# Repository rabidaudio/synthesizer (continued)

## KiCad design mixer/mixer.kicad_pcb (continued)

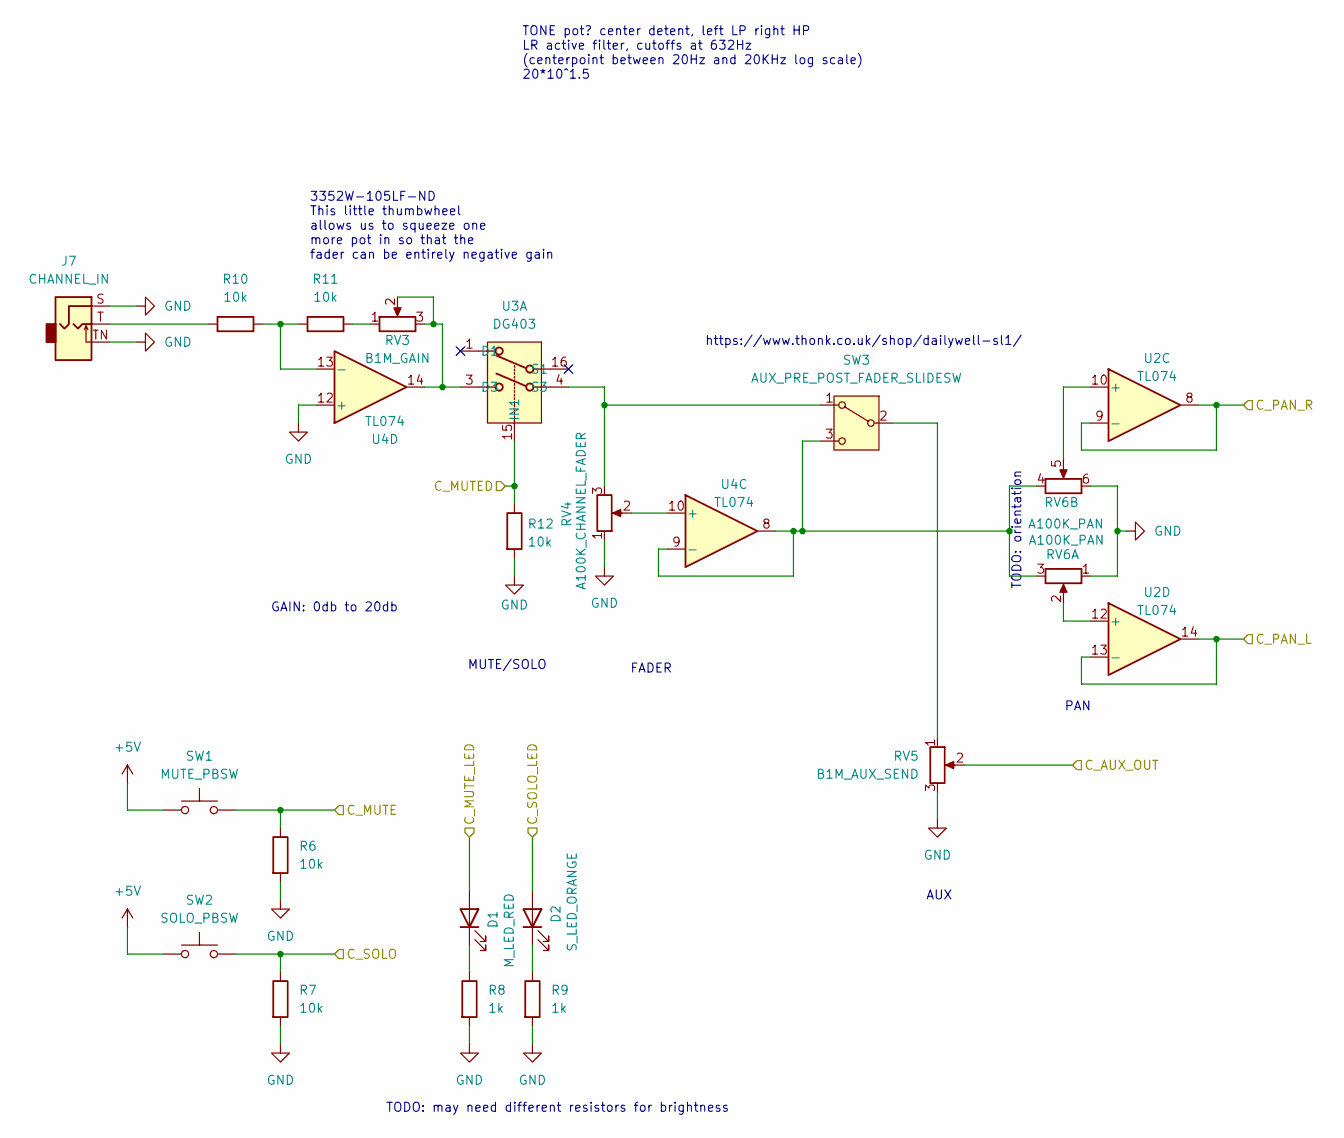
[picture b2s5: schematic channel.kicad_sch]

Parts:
D1: M_LED_RED; LED_D2.0mm_W4.8mm_H2.5mm_FlatTop
D2: S_LED_ORANGE; LED_D2.0mm_W4.8mm_H2.5mm_FlatTop
J7: CHANNEL_IN; Jack_3.5mm_QingPu_WQP-PJ398SM_Vertical_CircularHoles
R6, R7, R10, R11, R12: 10k; R_0603_1608Metric
R8, R9: 1k; R_0603_1608Metric
RV3: B1M_GAIN; 3352W
RV4: A100K_CHANNEL_FADER; Potentiometer_Bourns_PTA3043_Single_Slide
RV5: B1M_AUX_SEND; Potentiometer_Alpha_RD901F-40-00D_Single_Vertical
RV6: A100K_PAN; Potentiometer_Alpha_RD902F-40-00D_Dual_Vertical_CircularHol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
SW1: MUTE_PBSW; SW_PUSH_6mm
SW2: SOLO_PBSW; SW_PUSH_6mm
SW3: AUX_PRE_POST_FADER_SLIDESW; Dailywell SPDT Sub-Mini Slide SW
U2, U4: TL074; SOIC-14_3.9x8.7mm_P1.27mm
U3: DG403; SOIC-16_3.9x9.9mm_P1.27mm

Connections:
+5V: SW1.1, SW2.1; also elsewhere on the board
/Channel Module/C1_MUTE: R6.1, SW1.2; also elsewhere on the board
/Channel Module/C1_MUTED: R12.1, U3.15 (IN1); also elsewhere on the board
/Channel Module/C1_MUTE_LED: D1.2 (A); also elsewhere on the board
/Channel Module/C1_SOLO: R7.1, SW2.2; also elsewhere on the board
/Channel Module/C2_MUTED: U3.10 (IN2); also elsewhere on the board
/Channel Module/C2_MUTE_LED: D2.2 (A); also elsewhere on the board
/Channel Module/Channel1/C_AUX_OUT: RV5.2; also elsewhere on the board
/Channel Module/Channel1/C_PAN_L: U2.13 (-), U2.14; also elsewhere on the board
/Channel Module/Channel1/C_PAN_R: U2.8, U2.9 (-); also elsewhere on the board
/Channel Module/Channel2/C_PAN_L: U2.1, U2.2 (-); also elsewhere on the board
/Channel Module/Channel2/C_PAN_R: U2.6 (-), U2.7; also elsewhere on the board
GND: J7.S, J7.TN, R6.2, R7.2, R8.2, R9.2, R12.2, RV4.1, RV5.3, RV6.1, RV6.6, U4.3 (+), U4.12 (+); also elsewhere on the board
unnamed: D1.1 (K), R8.1
unnamed: D2.1 (K), R9.1
unnamed: J7.T, R10.1
unnamed: R11.2, RV3.1
unnamed: RV4.3, SW3.1 (A), U3.4 (S3)
unnamed: RV5.1, SW3.2 (B)
unnamed: RV6.3, RV6.4, SW3.3 (C), U4.8, U4.9 (-)
unnamed 55: U3.5 (S4); also elsewhere on the board
unnamed 57: U4.6 (-), U4.7; also elsewhere on the board
unnamed 58: U2.3 (+); also elsewhere on the board
unnamed 59: U2.5 (+); also elsewhere on the board
unnamed: RV6.5, U2.10 (+)
unnamed: RV6.2, U2.12 (+)
unnamed: RV3.2, RV3.3, U3.3 (D3), U4.14
unnamed 63: U3.6 (D4), U4.1; also elsewhere on the board
unnamed 64: U4.2 (-); also elsewhere on the board
unnamed 65: U4.5 (+); also elsewhere on the board
unnamed: RV4.2, U4.10 (+)
unnamed: R10.2, R11.1, U4.13 (-)

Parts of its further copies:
D3: M_LED_RED; LED_D2.0mm_W4.8mm_H2.5mm_FlatTop
D4: S_LED_ORANGE; LED_D2.0mm_W4.8mm_H2.5mm_FlatTop
J9: CHANNEL_IN; Jack_3.5mm_QingPu_WQP-PJ398SM_Vertical_CircularHoles
R25, R26, R29, R30, R31: 10k; R_0603_1608Metric
R27, R28: 1k; R_0603_1608Metric
RV7: B1M_GAIN; 3352W
RV8: A100K_CHANNEL_FADER; Potentiometer_Bourns_PTA3043_Single_Slide
RV9: B1M_AUX_SEND; Potentiometer_Alpha_RD901F-40-00D_Single_Vertical
RV10: A100K_PAN; Potentiometer_Alpha_RD902F-40-00D_Dual_Vertical_CircularHol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
SW4: MUTE_PBSW; SW_PUSH_6mm
SW5: SOLO_PBSW; SW_PUSH_6mm
SW6: AUX_PRE_POST_FADER_SLIDESW; Dailywell SPDT Sub-Mini Slide SW

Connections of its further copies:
+5V: SW4.1, SW5.1; also elsewhere on the board
/Channel Module/C1_SOLO_LED: D3.2 (A); also elsewhere on the board
/Channel Module/C2_MUTE: R25.1, SW4.2; also elsewhere on the board
/Channel Module/C2_MUTED: R31.1; also elsewhere on the board
/Channel Module/C2_SOLO: R26.1, SW5.2; also elsewhere on the board
/Channel Module/C2_SOLO_LED: D4.2 (A); also elsewhere on the board
/Channel Module/Channel2/C_AUX_OUT: RV9.2; also elsewhere on the board
GND: J9.S, J9.TN, R25.2, R26.2, R27.2, R28.2, R31.2, RV8.1, RV9.3, RV10.1, RV10.6; also elsewhere on the board
unnamed: D3.1 (K), R27.1
unnamed: D4.1 (K), R28.1
unnamed: J9.T, R29.1
unnamed: R30.2, RV7.1
unnamed 55: RV8.3, SW6.1 (A); also elsewhere on the board
unnamed: RV9.1, SW6.2 (B)
unnamed 57: RV10.3, RV10.4, SW6.3 (C); also elsewhere on the board
unnamed 58: RV10.2; also elsewhere on the board
unnamed 59: RV10.5; also elsewhere on the board
unnamed 63: RV7.2, RV7.3; also elsewhere on the board
unnamed 64: R29.2, R30.1; also elsewhere on the board
unnamed 65: RV8.2; also elsewhere on the board

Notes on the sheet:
MUTE/SOLO
PAN
TODO: orientation
GAIN: 0db to 20db
AUX
FADER
3352W-105LF-ND This little thumbwheel allows us to squeeze one more pot in so that the fader can be entirely negative gain
TODO: may need different resistors for brightness
TONE pot? center detent, left LP right HP LR active filter, cutoffs at 632Hz (centerpoint between 20Hz and 20KHz log scale) 20*10^1.5
https://www.thonk.co.uk/shop/dailywell-sl1/

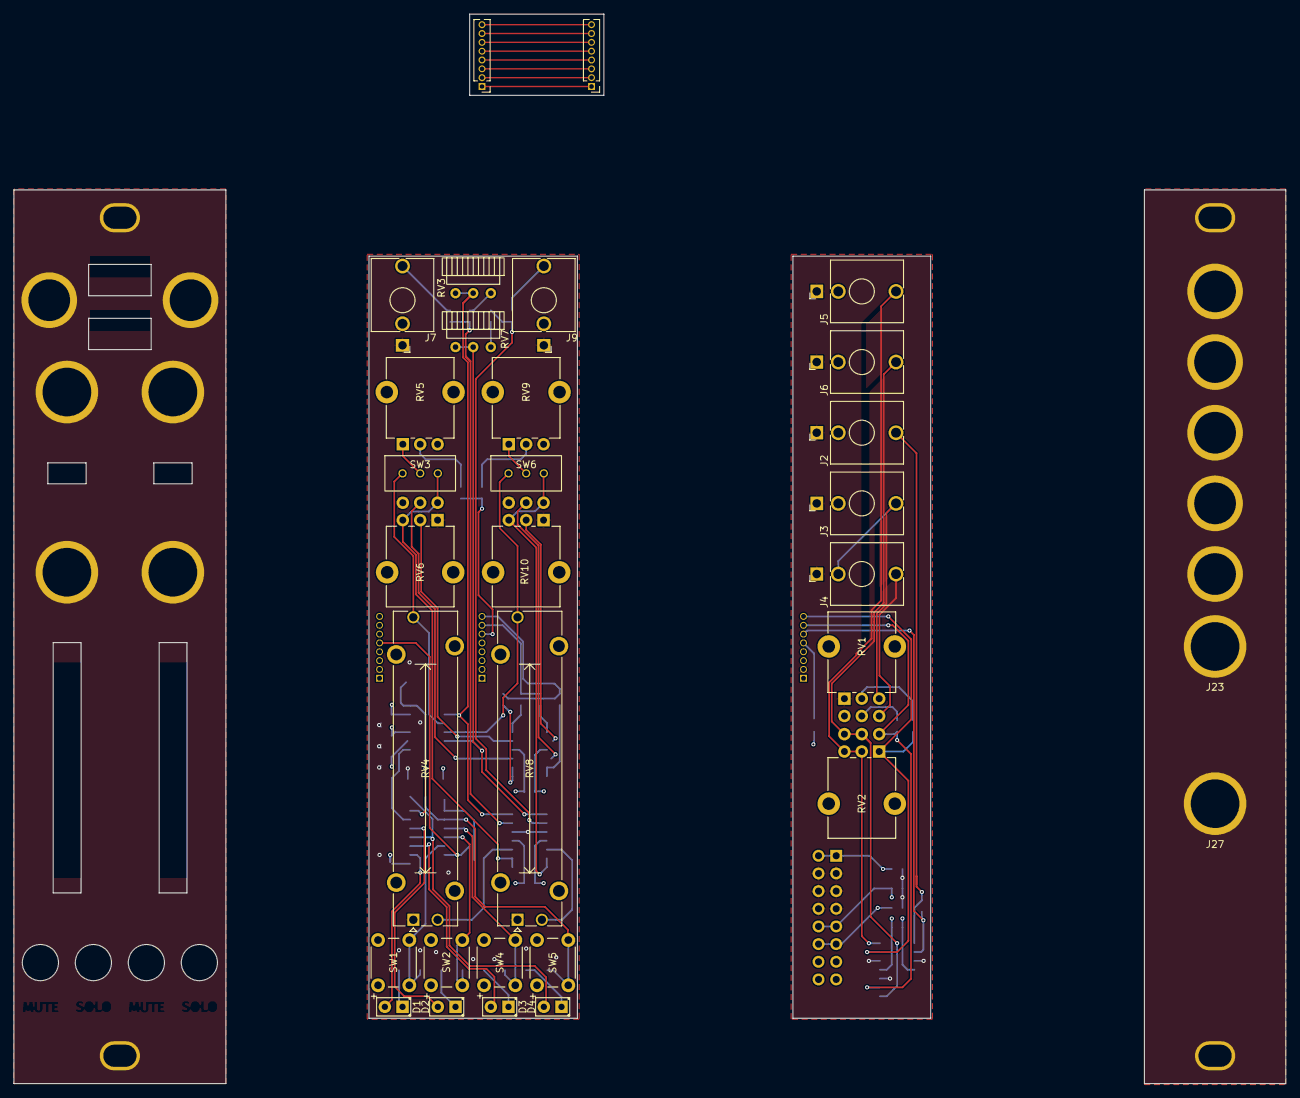
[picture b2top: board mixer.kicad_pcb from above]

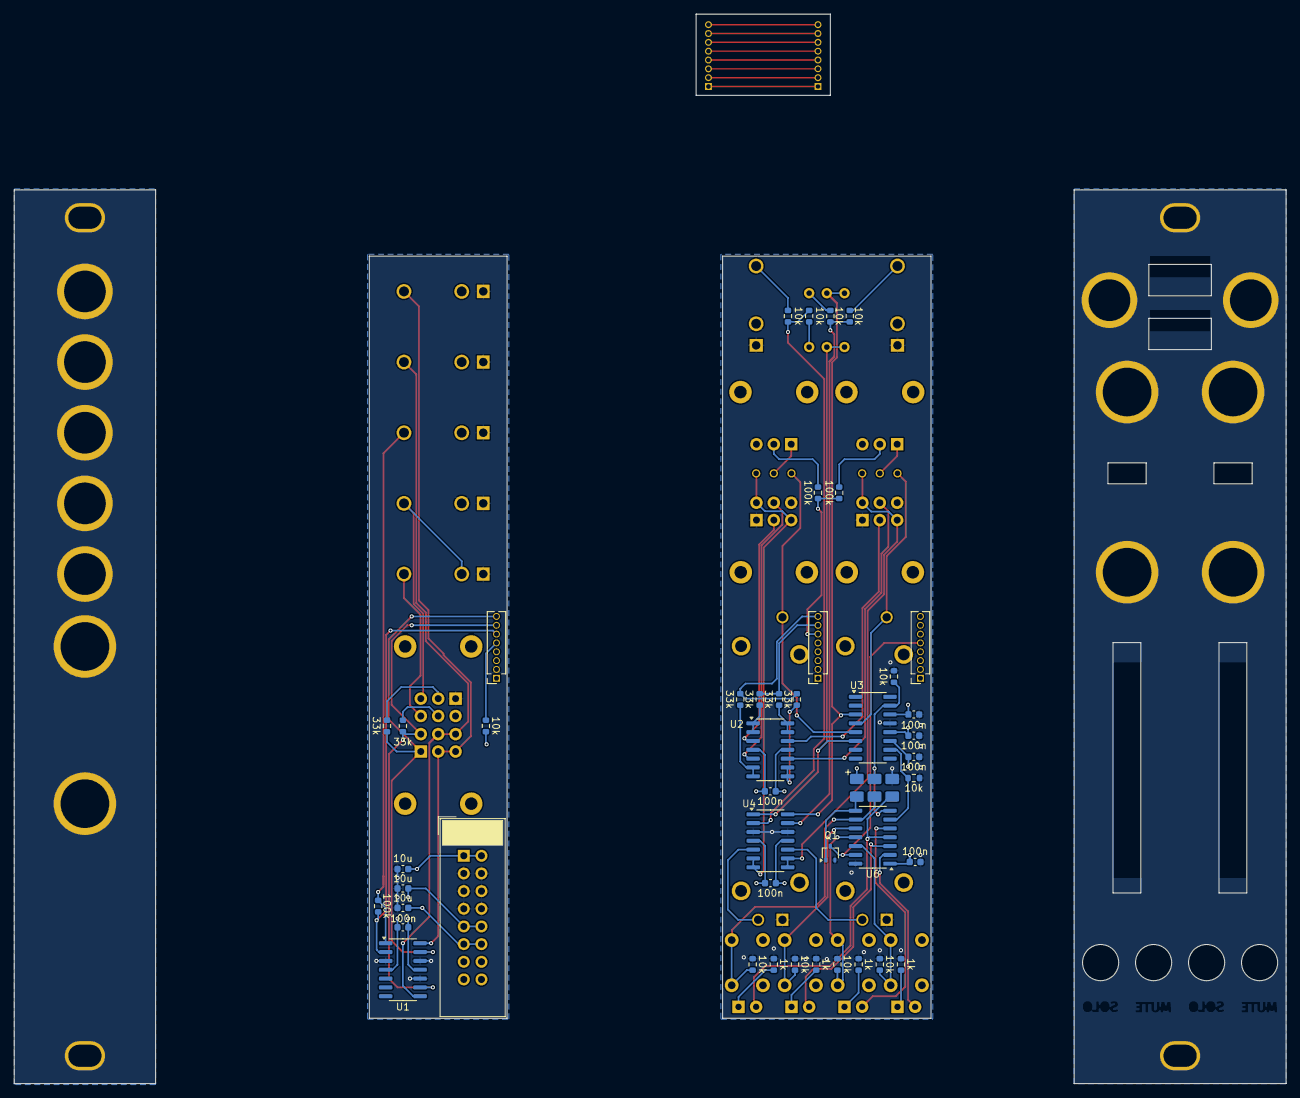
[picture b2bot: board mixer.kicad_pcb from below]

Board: 4 copper layers, 182.9 x 153.8 mm, 99 parts (45 on the bottom side), 68 nets.

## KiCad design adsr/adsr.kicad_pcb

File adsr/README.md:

# ADSR Envelope

This circuit operates by using the LM13700 as a variable current source charging
a capacitor. It is configured as a non-inverting op-amp charging the capacitor
to a reference voltage `V_ref` at the `+` pin with a slew rate limited by the current
control. The capacitor's voltage will change linearly based on `I_abc` until it settles
at `V_ref`. Then a bit of digital logic to create a 3-state state machine to select the
correct  `V_ref` and `I_abc`.

States:

- Attack: `V_gate=5V`, `V_ref=V_in`, `I_abc` controlled by `R_attack`
- Decay: `V_gate=5V`, `V_ref=V_sustain`, `I_abc` controlled by `R_decay`
- Release: `V_gate=0`, `V_ref=0`, `I_abc` controlled by `R_release`

The Attack, Decay, and Release knobs control `I_abc` in each state,
while the Sustain knob divides down `V_in` to set `V_ref` in the
Decay state.

A comparator, capacitor, and a few transistors create cheap analog
a flip-flop that turns on when the output hits `V_in` (flipping from
the Attack state to the Decay state), and turns off when `V_gate`
turns off.

Voltage control of the parameters could be possible by exposing
access to `I_abc`, but it doesn't make much sense to me to expose
those parameters with any control other than a knob - it's not the
kind of thing you need to modulate automatically.

Choice of the capacitor and the knob resistance control the time
range. Large values for both mean a longer charge time, but a large
capacitance effects the fastest charge time too, since `I_abc` is
capped at 2mA. Pot size effects dynamic range.

In practice, charge times less than 15ms are undetectable, and charge times above 2s are largely unnecessary.

A non-linear resistance would allow finer control at larger charge times. However linear seems to have plenty of expressiveness.

C=4.7u and a knob range of 1M gives a control range of 12ms to \~1.8s for a
0-5V change, i.e. a slew rate between 356 V/s and 2.4 V/s.

Could offer two caps, fast and slow, with a toggle switch. A 22u capacitor gives 58ms to 8.6s. A 1u capacitor gives \~5ms to \~55ms.

A current mirror isolates the 3 different reference voltages, without it they
interfere with each other.

Rates are dependant on the input level. This means if the input gate level is variable (for example it depends on MIDI note velocity), then the times will be slower for harder hits. We'd probably want constant rates regardless of velocity for example. However this seems difficult to achieve with the current design, as during release the input voltage is off, so without memory you don't have a reference to scale the output by.

**TODO: power usage**

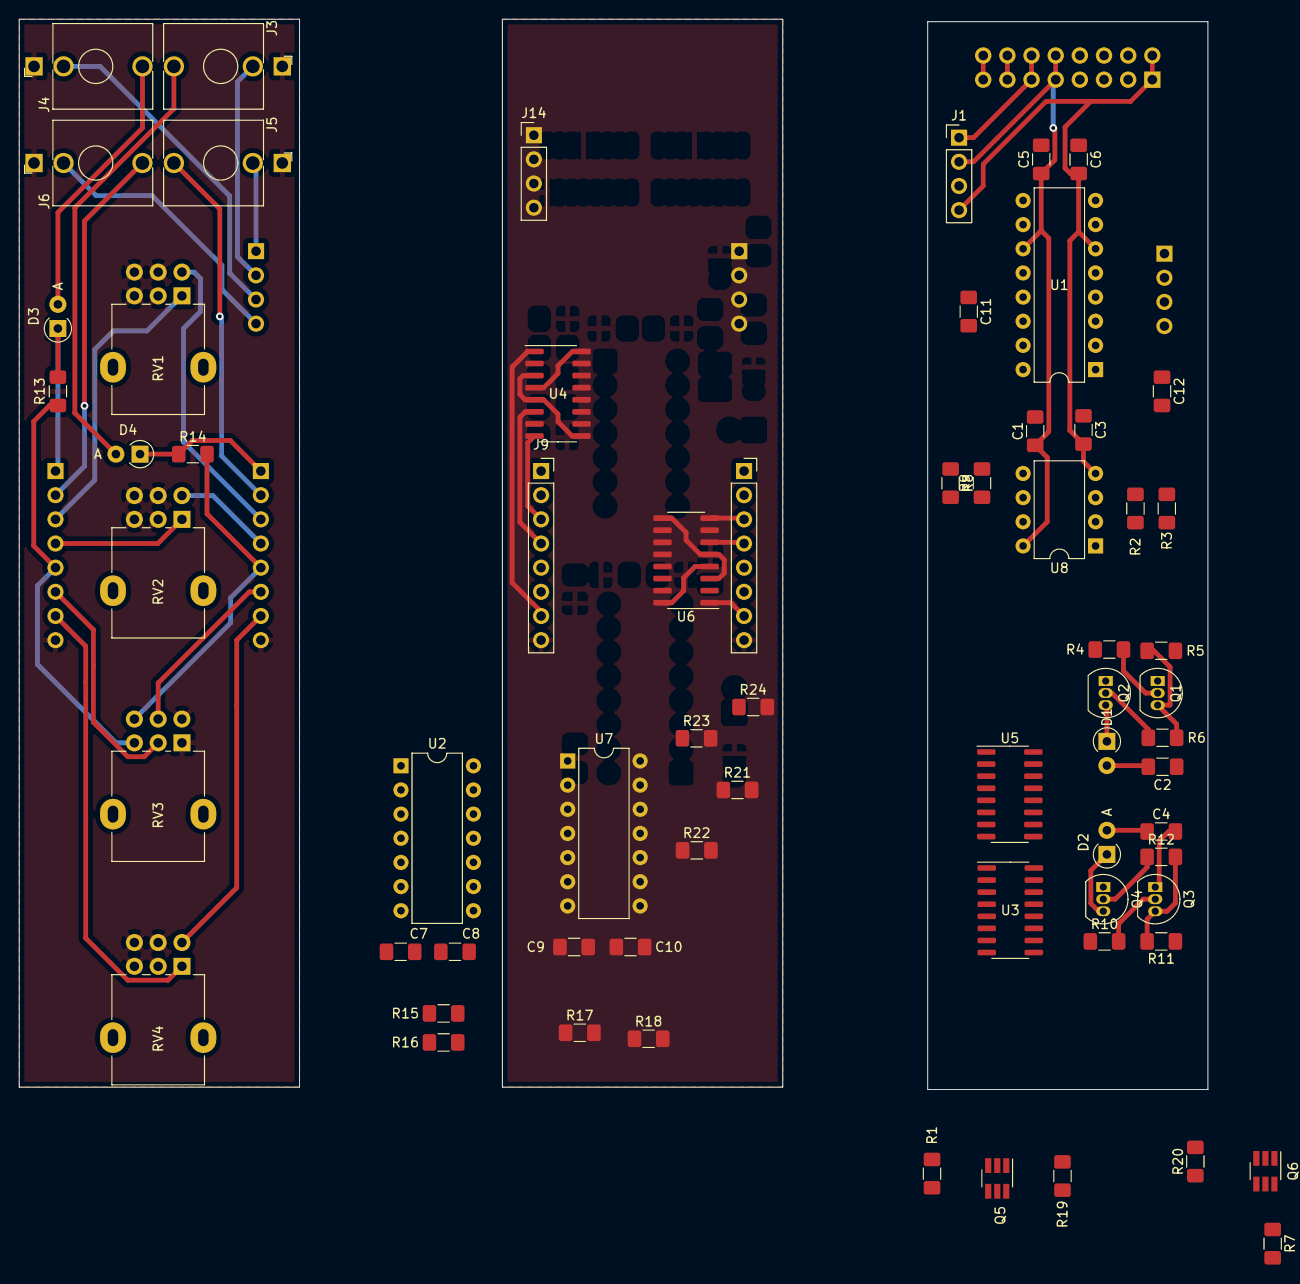
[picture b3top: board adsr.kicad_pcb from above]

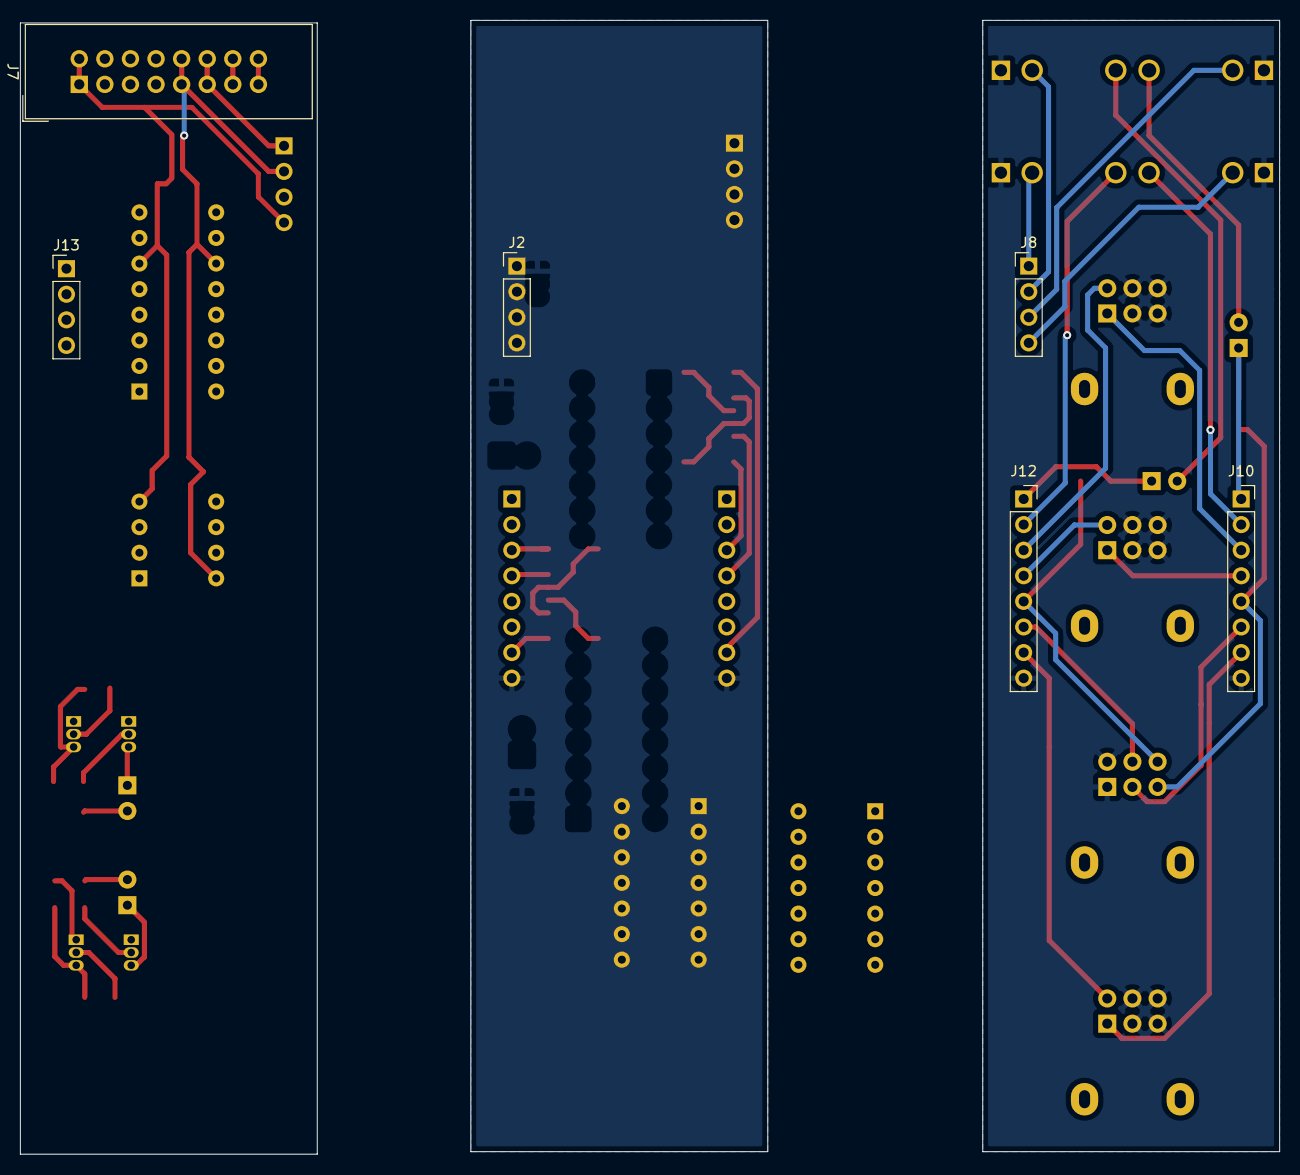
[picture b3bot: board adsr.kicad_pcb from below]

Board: 2 copper layers, 125.0 x 112.5 mm, 72 parts (6 on the bottom side), 64 nets.

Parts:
C1, C3, C5, C6, C7, C8, C9, C10: 0.1u; C_1206_3216Metric_Pad1.42x1.75mm_HandSolder
C2, C4: 100n; C_1206_3216Metric_Pad1.42x1.75mm_HandSolder
C11, C12: 4.7u; C_1206_3216Metric_Pad1.42x1.75mm_HandSolder
D1, D2, D3, D4: D; D_A-405_P2.54mm_Vertical_AnodeUp
J1: Conn_01x04_Female; PinHeader_1x04_P2.54mm_Vertical
J2, J8, J13, J14: Conn_01x04_Male; PinHeader_1x04_P2.54mm_Vertical
J3: B_IN; Jack_3.5mm_QingPu_WQP-PJ398SM_Vertical_CircularHoles
J4: A_IN; Jack_3.5mm_QingPu_WQP-PJ398SM_Vertical_CircularHoles
J5: B_OUT; Jack_3.5mm_QingPu_WQP-PJ398SM_Vertical_CircularHoles
J6: A_OUT; Jack_3.5mm_QingPu_WQP-PJ398SM_Vertical_CircularHoles
J7: EURORACK_CONN_16; EURORACK_16_IDC
J9, J11: Conn_01x08_Female; PinSocket_1x08_P2.54mm_Vertical
J10, J12: Conn_01x08_Male; PinSocket_1x08_P2.54mm_Vertical
Q1, Q2, Q3, Q4: 2N3904; TO-92_Inline
Q5, Q6: DMMT5401; SOT-23-6_Handsoldering
R1, R7, R19, R20: 6.8k; R_1206_3216Metric_Pad1.42x1.75mm_HandSolder
R2, R6, R8, R12, R21, R23: 1K; R_1206_3216Metric_Pad1.42x1.75mm_HandSolder
R3, R4, R5, R9, R10, R11, R22, R24: 100K; R_1206_3216Metric_Pad1.42x1.75mm_HandSolder
R13, R14: 1M; R_1206_3216Metric_Pad1.42x1.75mm_HandSolder
R15, R16, R17, R18: 10K; R_1206_3216Metric_Pad1.42x1.75mm_HandSolder
RV1: R_ATTACK; Potentiometer_Alpha_RD902F-40-00D_Dual_Vertical
RV2: R_DECAY; Potentiometer_Alpha_RD902F-40-00D_Dual_Vertical
RV3: R_SUSTAIN; Potentiometer_Alpha_RD902F-40-00D_Dual_Vertical
RV4: R_RELEASE; Potentiometer_Alpha_RD902F-40-00D_Dual_Vertical
U1: LM13700; DIP-16_W7.62mm
U2, U7: TL074; DIP-14_W7.62mm
U3, U4, U5, U6: DG403; SOIC-16_3.9x9.9mm_P1.27mm
U8: TL072; DIP-8_W7.62mm

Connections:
+5V: J1.1, J7.11 (5V), J14.4, U3.12 (VL), U4.12 (VL), U5.12 (VL), U6.12 (VL)
+12V: C1.1, C5.1, C7.1, C9.1, J1.2, J7.9 (12V_P), J14.3, Q5.5 (E2), Q5.6 (E1), Q6.5 (E2), Q6.6 (E1), R5.1, R11.1, R22.2, R24.2, U1.11 (V+), U2.4 (V+), U3.11 (V+), U4.11 (V+), U5.11 (V+), U6.11 (V+), U7.4 (V+), U8.8 (V+)
-12V: C3.2, C6.2, C8.2, C10.2, J1.4, J7.1 (12V_N), J14.1, U1.6 (V-), U2.11 (V-), U3.14 (V-), U4.14 (V-), U5.14 (V-), U6.14 (V-), U7.11 (V-), U8.4 (V-)
/envelope/ATTACK: J9.3, J10.3, RV1.1, U4.8 (D2)
/envelope/DECAY: J9.4, J10.4, RV2.1, U4.6 (D4)
/envelope/IN_RAW: D3.1 (K), J9.1, J10.1, R13.1, U2.12 (+)
/envelope/REF: R2.1, U2.1, U2.2 (-), U3.8 (D2)
/envelope/REF_RAW: J9.5, J10.5, R13.2, RV3.3, U2.3 (+)
/envelope/RELEASE: J9.7, J10.7, RV4.1, U4.1 (D1)
/envelope/STATE: C2.1, D1.2 (A), U1.9, U3.10 (IN2), U4.10 (IN2)
/envelope/SUS: U2.6 (-), U2.7, U3.6 (D4)
/envelope/SUS_RAW: J9.6, J10.6, RV3.2, U2.5 (+)
/envelope/VC: C11.1, U1.12, U1.13 (-), U2.10 (+), U8.3 (+)
/envelope/VINS: R4.1, U2.14, U3.15 (IN1), U4.15 (IN1)
/sheet5F5D80AF/ATTACK: J11.3, J12.3, RV1.4, U6.8 (D2)
/sheet5F5D80AF/DECAY: J11.4, J12.4, RV2.4, U6.6 (D4)
/sheet5F5D80AF/IN_RAW: D4.1 (K), J11.1, J12.1, R14.1, U7.5 (+)
/sheet5F5D80AF/REF: R8.1, U5.8 (D2), U7.8, U7.9 (-)
/sheet5F5D80AF/REF_RAW: J11.5, J12.5, R14.2, RV3.6, U7.10 (+)
/sheet5F5D80AF/RELEASE: J11.7, J12.7, RV4.4, U6.1 (D1)
/sheet5F5D80AF/STATE: C4.1, D2.2 (A), U1.8, U5.10 (IN2), U6.10 (IN2)
/sheet5F5D80AF/SUS: U5.6 (D4), U7.13 (-), U7.14
/sheet5F5D80AF/SUS_RAW: J11.6, J12.6, RV3.5, U7.12 (+)
/sheet5F5D80AF/VC: C12.1, U1.4 (-), U1.5, U7.3 (+), U8.5 (+)
/sheet5F5D80AF/VINS: R10.1, U5.15 (IN1), U6.15 (IN1), U7.7
A_IN: D3.2 (A), J4.T
A_IN_DEFAULT: J2.3, J4.TN, J8.3, J13.3
A_OUT: J6.T, J9.2, J10.2, R16.2, U2.8
A_OUT_DEFAULT: J2.4, J6.TN, J8.4, J13.4
B_IN: D4.2 (A), J3.T
B_IN_DEFAULT: J2.2, J3.TN, J8.2, J13.2
B_OUT: J5.T, J11.2, J12.2, R18.2, U7.1
B_OUT_DEFAULT: J2.1, J5.TN, J8.1, J13.1
GND: C1.2, C2.2, C3.1, C4.2, C5.2, C6.1, C7.2, C8.1, C9.2, C10.1, C11.2, C12.2, J1.3, J3.S, J4.S, J5.S, J6.S, J7.3 (GND), J9.8, J10.8, J11.8, J12.8, J14.2, Q1.1 (E), Q2.1 (E), Q3.1 (E), Q4.1 (E), R3.2, R9.2, R15.1, R17.1, R21.2, R23.2, RV1.2, RV1.3, RV1.5, RV1.6, RV2.2, RV2.3, RV2.5, RV2.6, RV3.1, RV3.4, RV4.2, RV4.3, RV4.5, RV4.6, U3.1 (D1), U3.13 (GND), U4.13 (GND), U5.1 (D1), U5.13 (GND), U6.13 (GND)
unnamed: D1.1 (K), Q2.3 (C)
unnamed: D2.1 (K), Q4.3 (C)
unnamed: Q1.2 (B), R4.2
unnamed: Q1.3 (C), R5.2, R6.2
unnamed: Q2.2 (B), R6.1
unnamed: Q3.2 (B), R10.2
unnamed: Q3.3 (C), R11.2, R12.2
unnamed: Q4.2 (B), R12.1
unnamed: Q5.1 (C1), Q5.2 (B1), Q5.3 (B2), R19.1
unnamed: Q5.4 (C2), R1.1
unnamed: Q6.1 (C1), Q6.2 (B1), Q6.3 (B2), R20.1
unnamed: Q6.4 (C2), R7.1
unnamed: R1.2, U1.16
unnamed: R2.2, R3.1, U8.2 (-)
unnamed: R7.2, U1.1
unnamed: R8.2, R9.1, U8.6 (-)
unnamed: R15.2, R16.1, U2.9 (-)
unnamed: R17.2, R18.1, U7.2 (-)
unnamed: R19.2, U4.4 (S3), U4.16 (S1)
unnamed: R20.2, U6.4 (S3), U6.16 (S1)
unnamed: R21.1, R22.1, U2.13 (-)
unnamed: R23.1, R24.1, U7.6 (-)
unnamed: U1.3 (+), U5.4 (S3), U5.16 (S1)
unnamed: U1.7, U8.7
unnamed: U1.10, U8.1
unnamed: U1.14 (+), U3.4 (S3), U3.16 (S1)
unnamed: U3.3 (D3), U3.5 (S4), U3.9 (S2)
unnamed: U4.3 (D3), U4.5 (S4), U4.9 (S2)
unnamed: U5.3 (D3), U5.5 (S4), U5.9 (S2)
unnamed: U6.3 (D3), U6.5 (S4), U6.9 (S2)

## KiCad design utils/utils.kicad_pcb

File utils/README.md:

# Jackknife

> Buffer/Inverter/Gate/Adder/Scaler/Source

## Description

This is a collection of common tools for transforming signals, either control voltages or audio signals. While there are several distinct utilities, most are not mutually-exclusive.

### Source

When `A_IN` is disconnected, `OUT` is a constant voltage output based on the position of the knob. `OUT` is 0V when the knob is in the center position, and adjusts up to +/- 10V.

### Buffer / Scaler

When `A_IN` is supplied, it's value is buffered to `OUT`. The knob position linearly adjusts the output gain. At the center position, `OUT` is the same as `A_IN`. At the full-left position, `OUT` is off. At the full-right position, the value of `A_IN` is doubled. 

### Adder

When `B_IN` is supplied, it's value is added to `A_IN` before applying scaling.

### Inverter

`~OUT` is always the inverse of `OUT`.

### Gate

When `GATE` is supplied with a digital voltage, it allows disabling `OUT` (and `~OUT`) at logic-low (0V). An LED indicates when the gate is open. When `GATE` is not supplied, the outputs are always enabled, and the LED remains off.

### Digital logic

Digital `OR` can be implemented by summing signals on `A_IN` and `B_IN` With the knob at the 1/4 position. Digital `AND` can be implemented by applying one signal to `A_IN` and one to `GATE` with the knob at the 1/2 position.

## Design

A summing inverting amplifier with a variable feedback resistor handles the adder, inverter, and scalar. A connection on either A or B toggles an analog switch selecting between a constant voltage source and the summing output. Another
analog switch controlled by the gate allows that signal to be toggled before it is buffered in both an inverted and
re-inverted back to positive outputs.

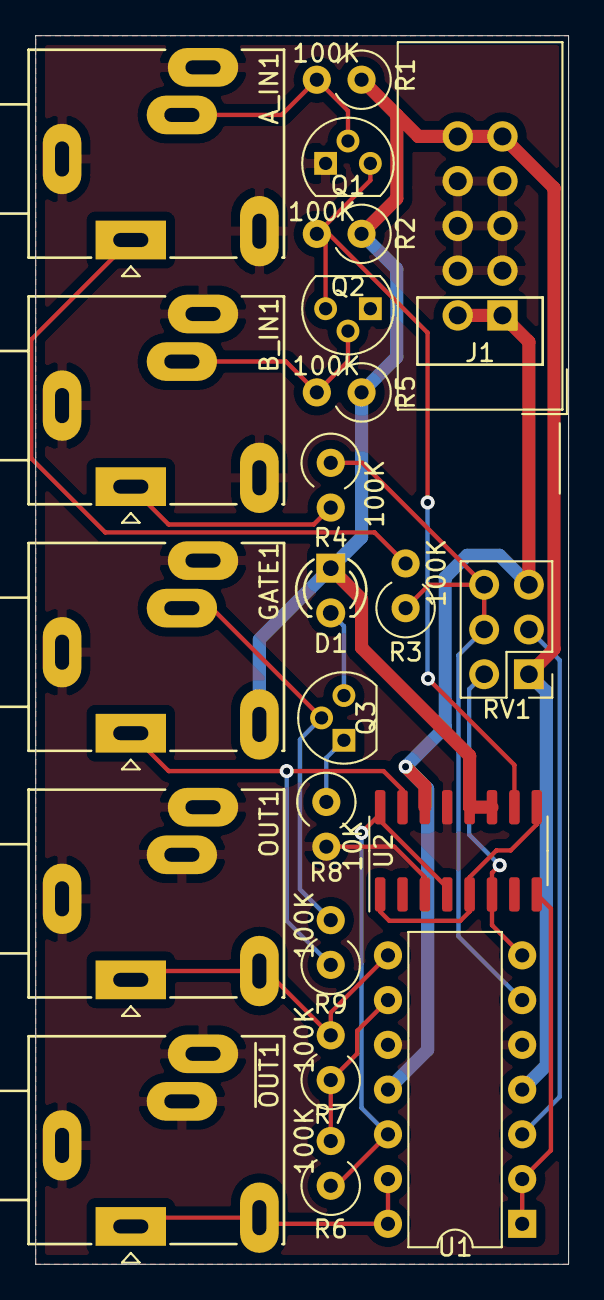
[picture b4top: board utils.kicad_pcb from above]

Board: 2 copper layers, 30.2 x 69.8 mm, 21 parts (0 on the bottom side), 21 nets.

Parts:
A_IN1: AudioJack2_Ground_Switch; Jack_3.5mm_Ledino_KB3SPRS_Horizontal
B_IN1: AudioJack2_Ground_Switch; Jack_3.5mm_Ledino_KB3SPRS_Horizontal
D1: LED; LED-3MM-SQUARE-ANODE
GATE1: AudioJack2_Ground_Switch; Jack_3.5mm_Ledino_KB3SPRS_Horizontal
J1: EURORACK_CONN_10; EURORACK_10_IDC
OUT1: AudioJack2_Ground_Switch; Jack_3.5mm_Ledino_KB3SPRS_Horizontal
Q1, Q2, Q3: 2N3904; TO-92
R1, R2, R3, R4, R5, R6, R7, R9: 100K; R_Axial_DIN0309_L9.0mm_D3.2mm_P2.54mm_Vertical
R8: 10K; R_Axial_DIN0309_L9.0mm_D3.2mm_P2.54mm_Vertical
RV1: 200K; PinHeader_2x03_P2.54mm_Vertical
U1: TL074; DIP-14_W7.62mm
U2: DG403; SOIC-16_3.9x9.9mm_P1.27mm

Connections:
+12V: D1.2, GATE1.TN, J1.9, R1.1, R2.1, R5.1, RV1.1, U1.4, U2.11, U2.12
-12V: J1.1, RV1.3, U1.11, U2.14
AIN: A_IN1.T, R3.2
A_CONN: A_IN1.SN, Q1.2, R1.2
BIN: B_IN1.T, R4.2
B_CONN: B_IN1.SN, Q2.2, R5.2
CONST: Q1.3, Q2.3, R2.2, U2.10
GATE: GATE1.T, R7.1, U2.15
GATE_CONN: GATE1.SN, Q3.2, R7.2
GND: A_IN1.G, A_IN1.S, A_IN1.TN, B_IN1.G, B_IN1.S, B_IN1.TN, GATE1.G, GATE1.S, J1.3, OUT1.G, OUT1.S, OUT1.SN, Q1.1, Q2.1, R8.2, U1.5, U1.10, U2.3, U2.13
unnamed: D1.1, Q3.3
unnamed: Q3.1, R8.1
unnamed: R3.1, R4.1, RV1.5, RV1.6, U1.6
unnamed: R6.1, U1.12, U2.4, U2.16
unnamed: R6.2, R9.1, U1.9
unnamed: RV1.2, U1.3
unnamed: RV1.4, U1.7, U2.6
unnamed: U1.1, U1.2, U2.8
unnamed: U2.1, U2.5, U2.9
OUT: OUT1.T, OUT1.TN, R9.2, U1.8
~OUT: U1.13, U1.14

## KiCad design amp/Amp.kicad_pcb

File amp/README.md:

# VCA

> 4-channel amplifier

## Description

Control Voltage 0-10V with `10V -> Gain=1`, `0V -> Gain~=0`. Can be overdriven up to `11V -> Gain=2` (actually slightly less because it will clip). Output is about 9.2 dB/V, with 0V around -98 dB.

Control voltage inputs are summed with a control knob, which adjusts CV between 0V and 10V.

The 4 channels are connected to the 4 channels from the filter, unless an input is supplied.

The 4 channels are mixed down along with EXT-IN, an input for arbitrary external signals, such as those from another synth. In MIX mode, the result of the mix is sent to both left and right stereo outputs. in SPLIT mode, channels A and C go to the left channel output only, while B and D go to the right channel output only.

Both 1/4" TLS main and 3.2mm headphone outputs are available. **TODO: power calculation**

**TODO: power usage** 

## Design

The amplifier is designed around the [LM13700](../reference/datasheets/lm13700.pdf), with an [antilog converter](../reference/exponential.pdf) providing current control. Calculations of component values are [here](amp.xlsx).

The LM13700 acts as a linear amplifier when `Vd <= 20mV`. It's output is a current source given by the equation `Iout=0.5*Vd/Vt*Iabc` where `Vt=26mV` @ room temp. `Iabc` cannot exceed 2mA. Setting `Iabc=0.5mA` for unity gain puts `Iout=.192mA`. This can be converted back to a voltage with a resistor. `Rout=26kΩ `sets the overall voltage gain to unity.

## Tuning

1. Set CV-IN to 10V, and RV2 to completely off. Adjust RT1 until base of Q1A is 0V (or Q1 collectors are the same).
2. Adjust RT2 until the current through it is 0.5mA. One way to do this is to precicely measure the negative supply rail, and then adjust the resistance to match.
3. Set CV-IN to 0V, RV2 to completely on, and IN to 10V. Adjust RT3 until OUT is 10V (an overall gain of 1).

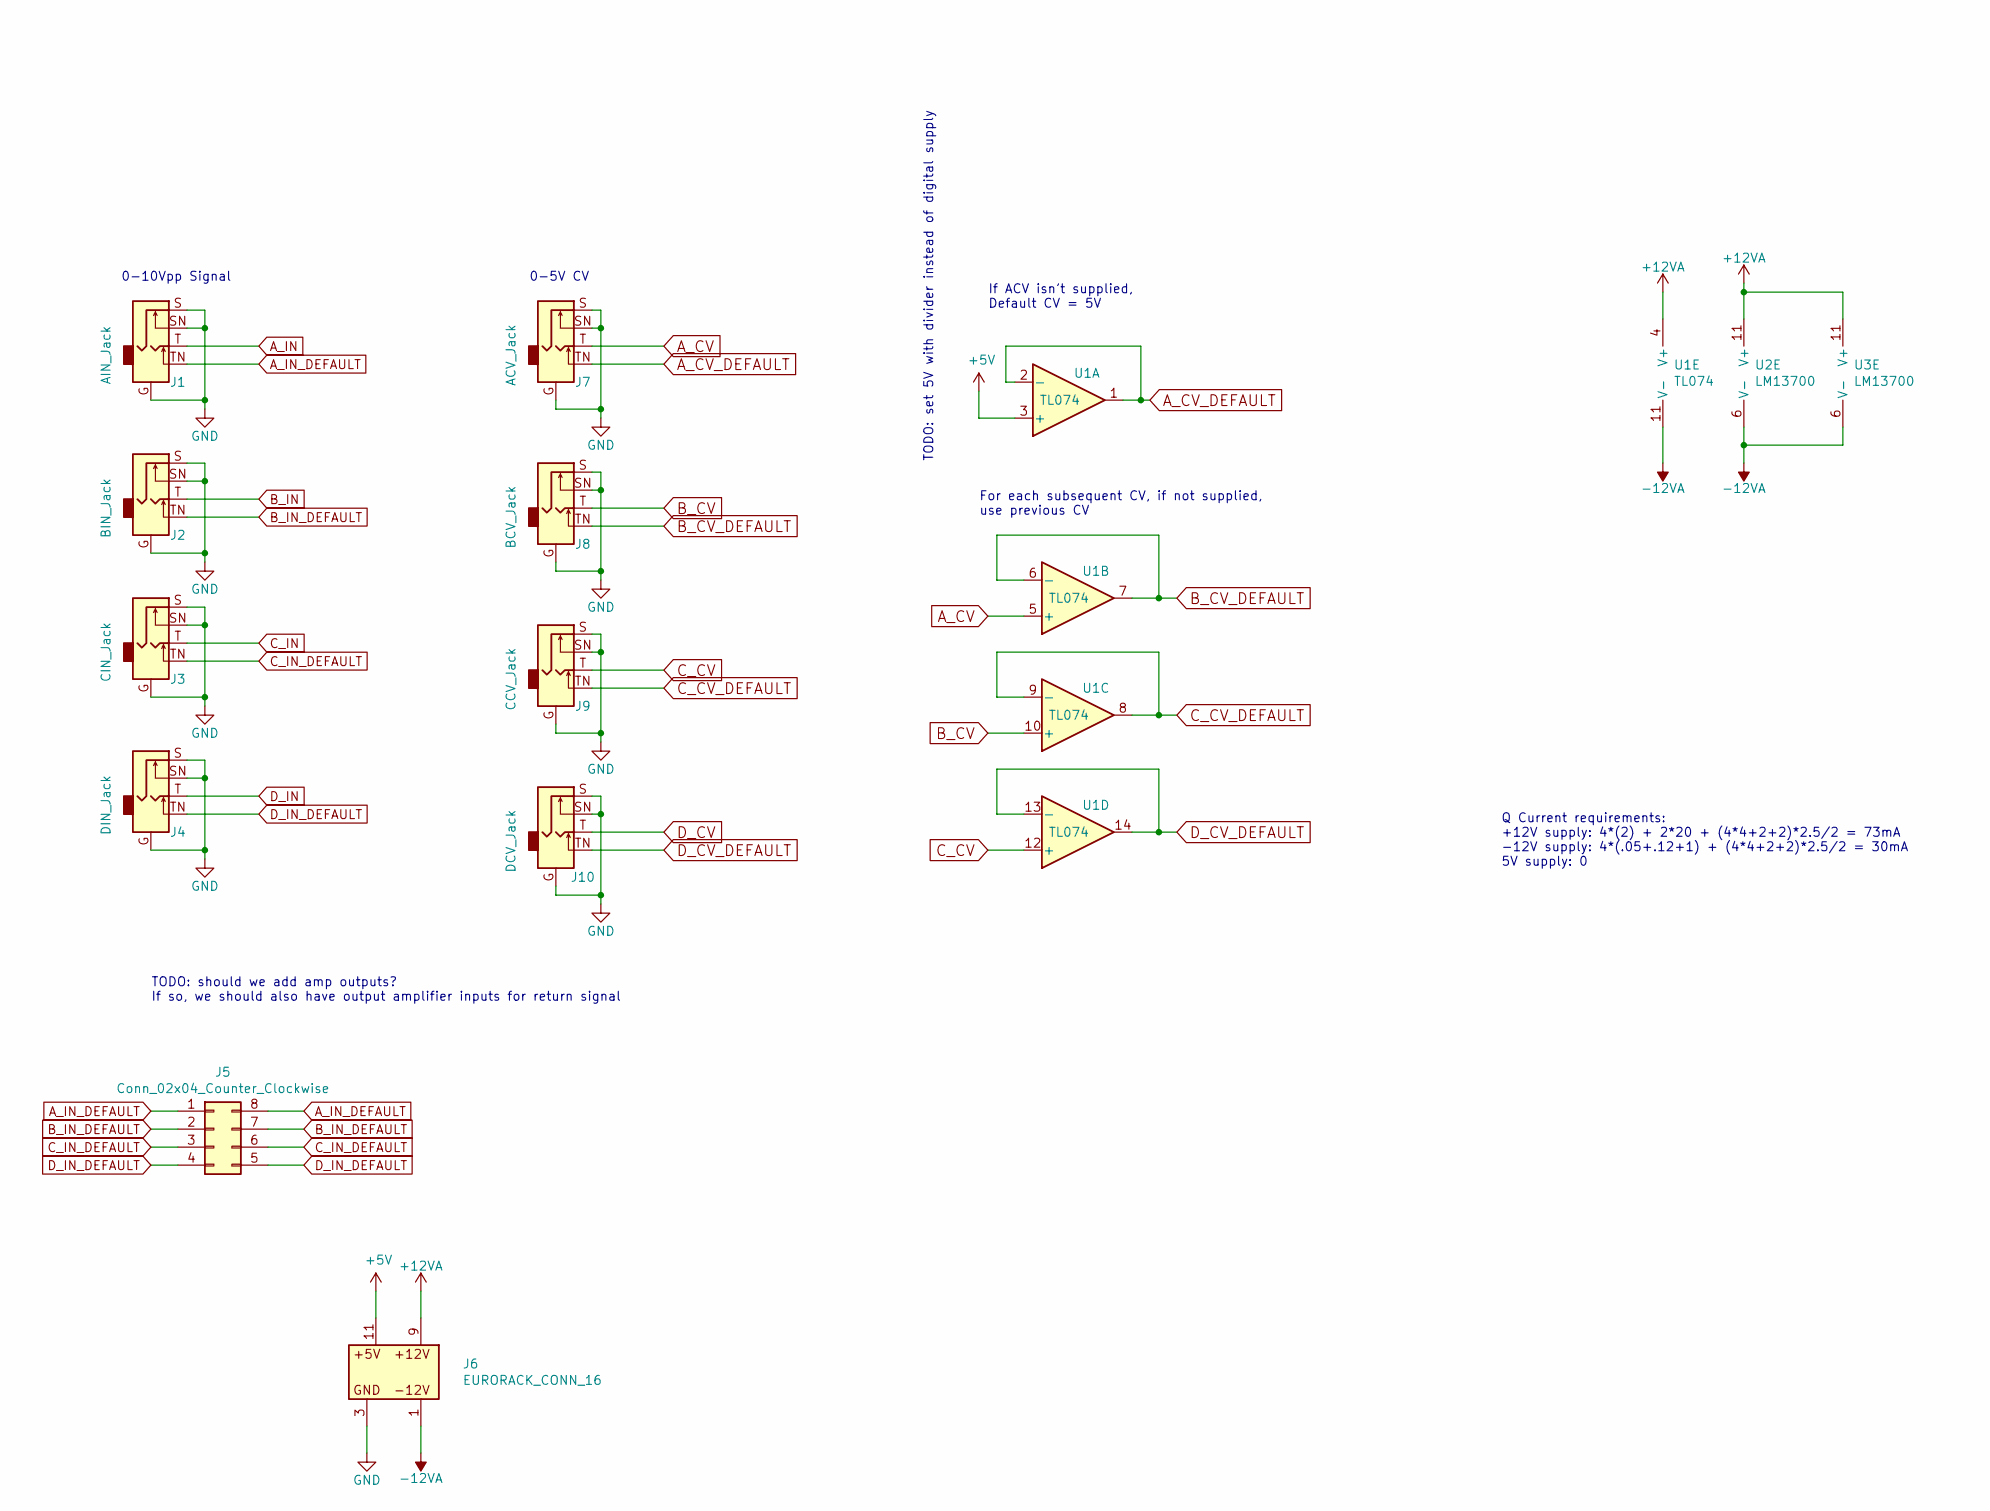
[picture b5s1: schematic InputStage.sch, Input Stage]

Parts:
J1: AIN_Jack; 3.5MM_Jack_Breakout_Vertical
J2: BIN_Jack; 3.5MM_Jack_Breakout_Vertical
J3: CIN_Jack; 3.5MM_Jack_Breakout_Vertical
J4: DIN_Jack; 3.5MM_Jack_Breakout_Vertical
J5: Conn_02x04_Counter_Clockwise; PinHeader_2x04_P2.54mm_Vertical
J6: EURORACK_CONN_16; EURORACK_16_IDC
J7: ACV_Jack; 3.5MM_Jack_Breakout_Vertical
J8: BCV_Jack; 3.5MM_Jack_Breakout_Vertical
J9: CCV_Jack; 3.5MM_Jack_Breakout_Vertical
J10: DCV_Jack; 3.5MM_Jack_Breakout_Vertical
U1: TL074; DIP-14_W7.62mm
U2, U3: LM13700; DIP-16_W7.62mm

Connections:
+5V: J6.11 (5V), U1.3 (+)
+12VA: J6.9 (12V_P), U1.4 (V+), U2.11 (V+), U3.11 (V+); also elsewhere on the board
-12VA: J6.1 (12V_N), U1.11 (V-), U2.6 (V-), U3.6 (V-); also elsewhere on the board
A_CV: J7.T, U1.5 (+); also elsewhere on the board
A_CV_DEFAULT: J7.TN, U1.1, U1.2 (-)
A_IN: J1.T; also elsewhere on the board
A_IN_DEFAULT: J1.TN, J5.1, J5.8
B_CV: J8.T, U1.10 (+); also elsewhere on the board
B_CV_DEFAULT: J8.TN, U1.6 (-), U1.7
B_IN: J2.T; also elsewhere on the board
B_IN_DEFAULT: J2.TN, J5.2, J5.7
C_CV: J9.T, U1.12 (+); also elsewhere on the board
C_CV_DEFAULT: J9.TN, U1.8, U1.9 (-)
C_IN: J3.T; also elsewhere on the board
C_IN_DEFAULT: J3.TN, J5.3, J5.6
D_CV: J10.T; also elsewhere on the board
D_CV_DEFAULT: J10.TN, U1.13 (-), U1.14
D_IN: J4.T; also elsewhere on the board
D_IN_DEFAULT: J4.TN, J5.4, J5.5
GND: J1.G, J1.S, J1.SN, J2.G, J2.S, J2.SN, J3.G, J3.S, J3.SN, J4.G, J4.S, J4.SN, J6.3 (GND), J7.G, J7.S, J7.SN, J8.G, J8.S, J8.SN, J9.G, J9.S, J9.SN, J10.G, J10.S, J10.SN, U2.4 (-), U3.4 (-); also elsewhere on the board
unnamed 60: U3.1; also elsewhere on the board
unnamed 63: U2.1; also elsewhere on the board
unnamed 91: U3.3 (+); also elsewhere on the board
unnamed 94: U3.5; also elsewhere on the board
unnamed 99: U2.3 (+); also elsewhere on the board
unnamed 102: U2.5; also elsewhere on the board

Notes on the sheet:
0-10Vpp Signal
If ACV isn’t supplied, Default CV = 5V
For each subsequent CV, if not supplied, use previous CV
0-5V CV
Q Current requirements: +12V supply: 4*(2) + 2*20 + (4*4+2+2)*2.5/2 = 73mA -12V supply: 4*(.05+.12+1) + (4*4+2+2)*2.5/2 = 30mA 5V supply: 0
TODO: should we add amp outputs? If so, we should also have output amplifier inputs for return signal
TODO: set 5V with divider instead of digital supply
